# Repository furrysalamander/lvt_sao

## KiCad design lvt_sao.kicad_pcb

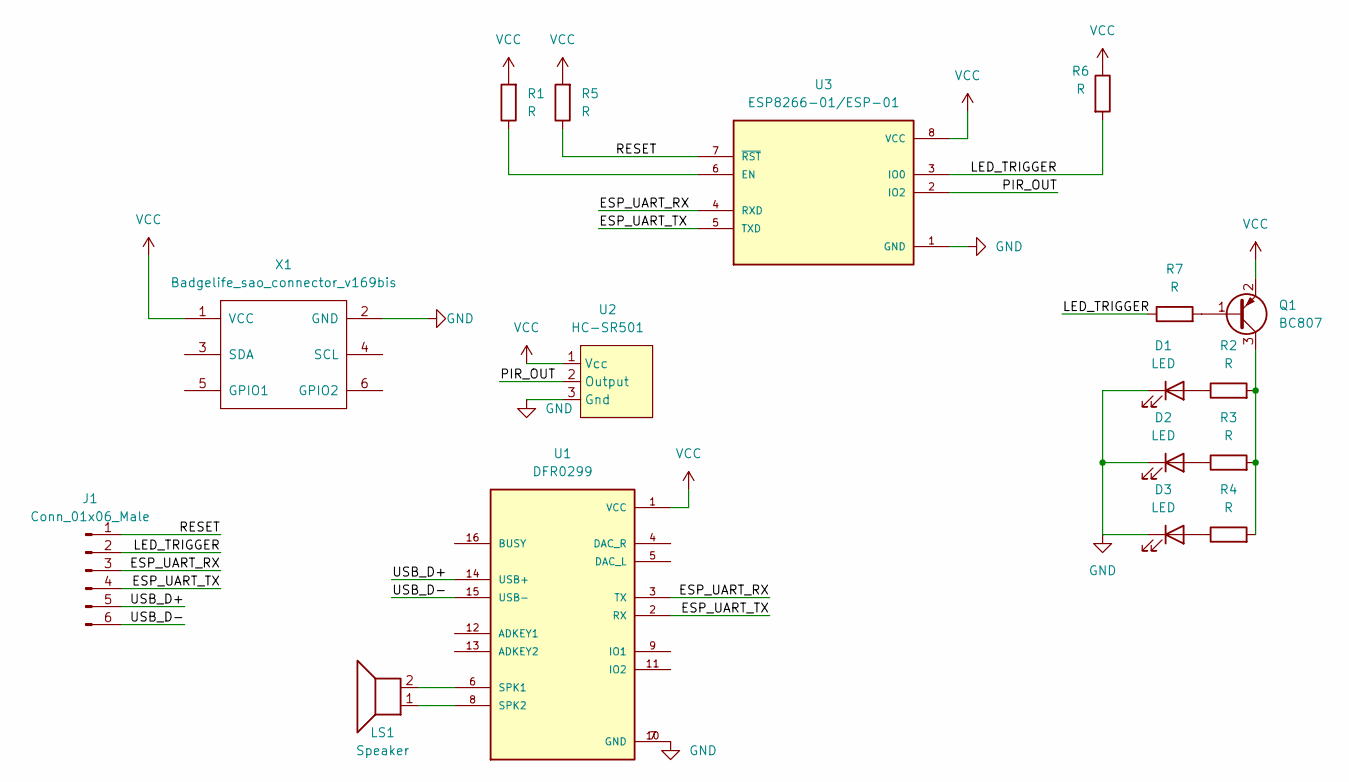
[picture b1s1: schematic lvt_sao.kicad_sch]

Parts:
D1, D2, D3: LED; LED_1210_3225Metric_Pad1.42x2.65mm_HandSolder
J1: Conn_01x06_Male; PinHeader_1x06_P2.54mm_Vertical_SMD_Pin1Left
LS1: Speaker; PinHeader_1x02_P2.54mm_Vertical_SMD_Pin1Left
Q1: BC807; SOT-23
R1, R2, R3, R4, R5, R6, R7: R; R_1210_3225Metric_Pad1.30x2.65mm_HandSolder
U1: DFR0299; MODULE_DFR0299
U2: HC-SR501
U3: ESP8266-01/ESP-01; XCVR_ESP8266-01_ESP-01; PARTREV V1.2
X1: Badgelife_sao_connector_v169bis; Badgelife-SAOv169-SAO-2x3

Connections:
/ESP_UART_RX: J1.3, U1.3 (TX), U3.4 (RXD)
/ESP_UART_TX: J1.4, U1.2 (RX), U3.5 (TXD)
/LED_TRIGGER: J1.2, R6.2, R7.1, U3.3 (IO0)
/PIR_OUT: U2.2 (Output), U3.2 (IO2)
/RESET: J1.1, R5.1, U3.7 (~RST)
/USB_D+: J1.5, U1.14 (USB+)
/USB_D-: J1.6, U1.15 (USB-)
GND: D1.1 (K), D2.1 (K), D3.1 (K), U1.7 (GND), U1.10 (GND), U2.3 (Gnd), U3.1 (GND), X1.2 (GND)
unnamed: D1.2 (A), R2.1
unnamed: D2.2 (A), R3.1
unnamed: D3.2 (A), R4.1
unnamed: LS1.1, U1.8 (SPK2)
unnamed: LS1.2, U1.6 (SPK1)
unnamed: Q1.1 (B), R7.2
unnamed: Q1.3 (C), R2.2, R3.2, R4.2
unnamed: R1.1, U3.6 (EN)
VCC: Q1.2 (E), R1.2, R5.2, R6.1, U1.1 (VCC), U2.1 (Vcc), U3.8 (VCC), X1.1 (VCC)

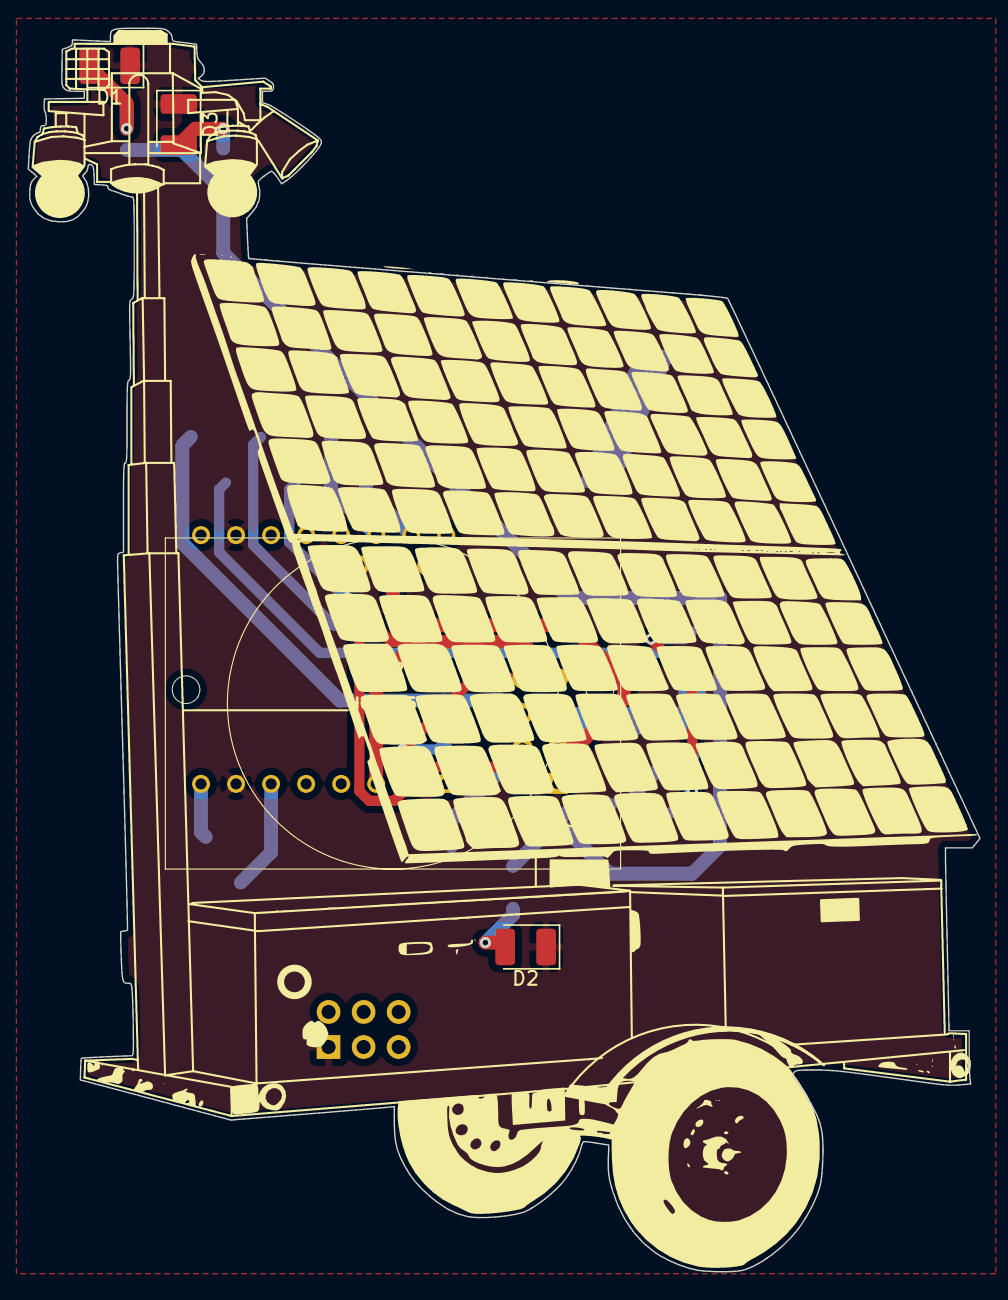
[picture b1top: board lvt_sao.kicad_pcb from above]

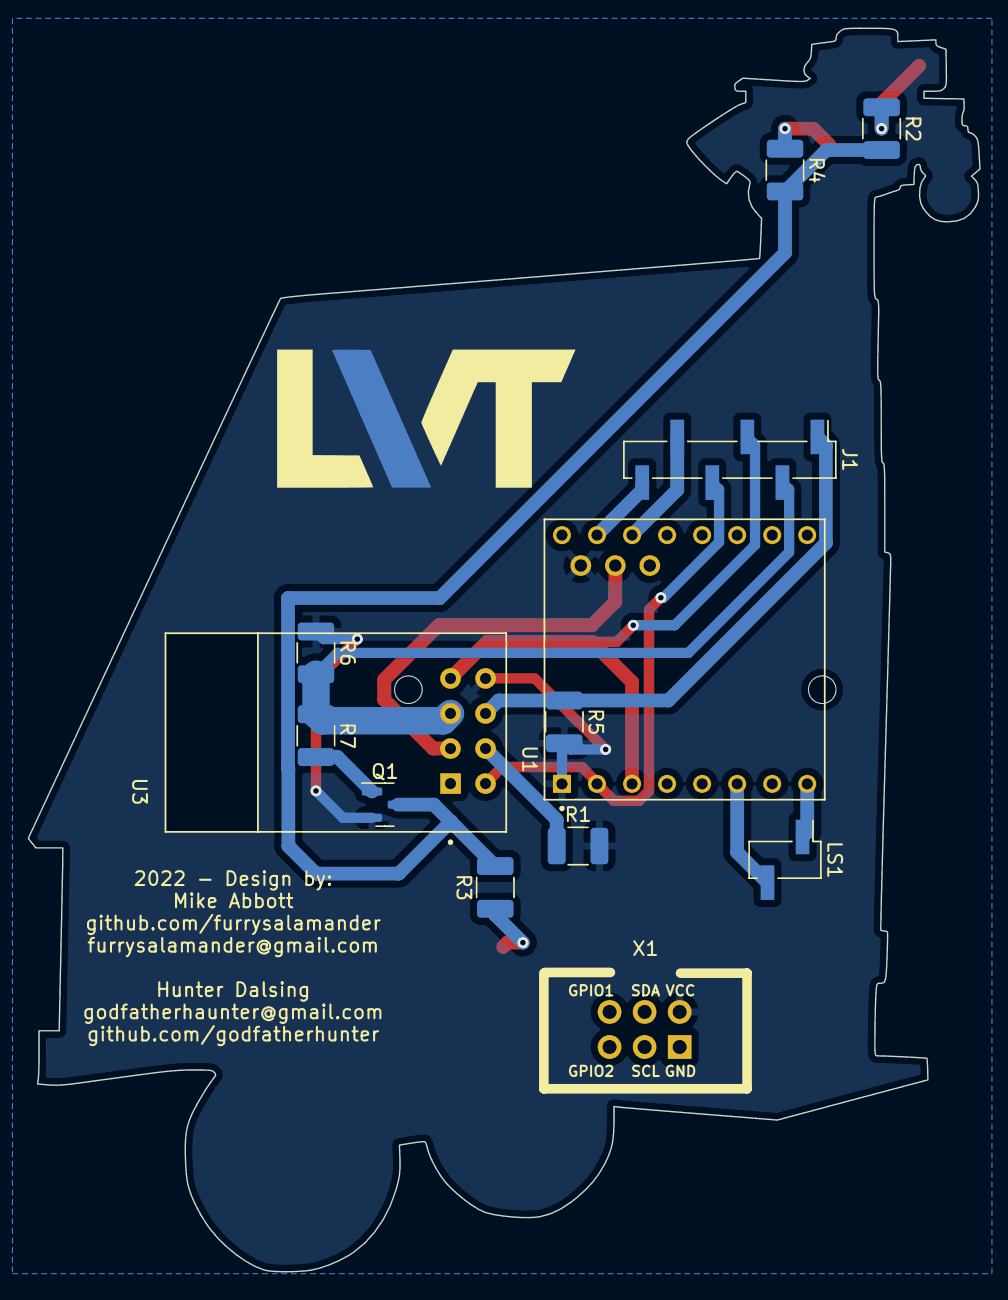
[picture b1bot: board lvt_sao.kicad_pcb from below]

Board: 2 copper layers, 69.0 x 90.1 mm, 17 parts (12 on the bottom side), 17 nets.

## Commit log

2022-09-20 First Pass
2022-10-09 Cleaned up the board and added graphics
2022-10-09 Made it pretty
2022-10-09 Components arranged and traces added
2022-11-19 final revision before ordering
